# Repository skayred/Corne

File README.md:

# Budget Wireless Corne Keyboard Build

A DIY wireless split keyboard based on the Corne layout, built for approximately $25 USD. This project uses a ProMicro clone with nrf52840 chip, making it a cost-effective alternative to traditional wireless split keyboard builds.

## Features
- Fully wireless using Bluetooth
- Split ergonomic design (Corne layout)
- Low profile design for portability
- Battery-powered with power switch
- ZMK firmware
- Estimated battery life: 1+ month

## Bill of Materials

| Component | Quantity | Cost (USD) | Link |
|-----------|----------|------------|------|
| Controller boards (ProMicro nrf52840) | 2 | 6.82 | [AliExpress](https://a.aliexpress.com/_EIV3vwY) |
| Batteries | 2 | 4.20 | [AliExpress](https://a.aliexpress.com/_Eynt9TK) |
| Mechanical Switches | 50 | 7.47 | [AliExpress](https://a.aliexpress.com/_EGhMxEC) |
| Keycaps | Set | 3.79 | [Option 1](https://a.aliexpress.com/_EzQyNtA) / [Option 2](https://a.aliexpress.com/_EH8mNqs) |
| Diodes (1N4148) | 100 | 0.85 | [AliExpress](https://a.aliexpress.com/_EwZoG2G) |
| Slide Switches | 2 | 0.11 | |
| 3D Printed Parts | Set | 1.80 | Files provided |

**Total Cost**: $25.04 (excluding wires and screws)

## Current Keymap

## Build Instructions

### Prerequisites
- Basic soldering skills
- Access to a 3D printer
- Basic understanding of keyboard firmware

### Case Assembly
1. Print the case files (STL files provided in `3DFiles` directory)
2. Note: You may need to adjust the:
   - Battery compartment size
   - Slide switch holes

### Wiring
1. Wire switches in a matrix configuration
2. Connect diodes:
   - Direction matters (black line indicates cathode)
   - Use diode legs for the rows
   - Use separate wires for columns
3. Keep wiring clear of screw holes
4. Connect the battery:
   - GND to GND pin
   - Positive to one of the side legs on the slide switch
   - Middle pin of the slide switch to the RAW pin

### Pin Connections for Rows and Columns
The matrix configuration uses GPIO pins on the nRF52840 Pro Micro clone. Below are the connections:

#### Rows (Connected to `row-gpios`):
- Row 0: Pin 21
- Row 1: Pin 20
- Row 2: Pin 19
- Row 3: Pin 18

#### Columns (Connected to `col-gpios`):
- Column 0: Pin 2
- Column 1: Pin 7
- Column 2: Pin 6
- Column 3: Pin 5
- Column 4: Pin 4
- Column 5: Pin 3

These pins are defined in the firmware and are configured for GPIO matrix scanning.

### Firmware Setup
This keyboard uses ZMK firmware. The left half acts as the main controller that connects to your device.

To flash the firmware:
1. Double press the reset button
2. Board will appear as mass storage device
3. Flash the appropriate firmware file

If you forgot the keyboard from your device and can't reconnect:
1. Flash the `settings_reset-nice_nano_v2-zmk.uf2` file
2. Reflash the regular firmware
3. Pair

## Repository Structure
```
├── .github/workflows/
│   └── build.yml
├── 3DFiles/
│   ├── Case_Left.stl
│   ├── Case_Right.stl
│   └── PlateCorne.stl
├── config/
│   ├── boards/shields/corne/
│   │   ├── corne_left.conf
│   │   ├── corne_left.overlay
│   │   ├── corne_right.conf
│   │   ├── corne_right.overlay
│   │   ├── corne.conf
│   │   ├── corne.dtsi
│   │   ├── Kconfig.defconfig
│   │   └── Kconfig.shield
│   ├── corne.keymap
│   └── west.yml
├── firmware/
│   ├── corne_left-nice_nano_v2-zmk.uf2
│   ├── corne_right-nice_nano_v2-zmk.uf2
│   └── settings_reset-nice_nano_v2-zmk.uf2
└── zephyr/
    ├── module.yml
    └── build.yaml
```

## Known Issues
- Left side case may have warping issues if battery swells
- Slide switch holes may need adjustment based on your components

## Final result

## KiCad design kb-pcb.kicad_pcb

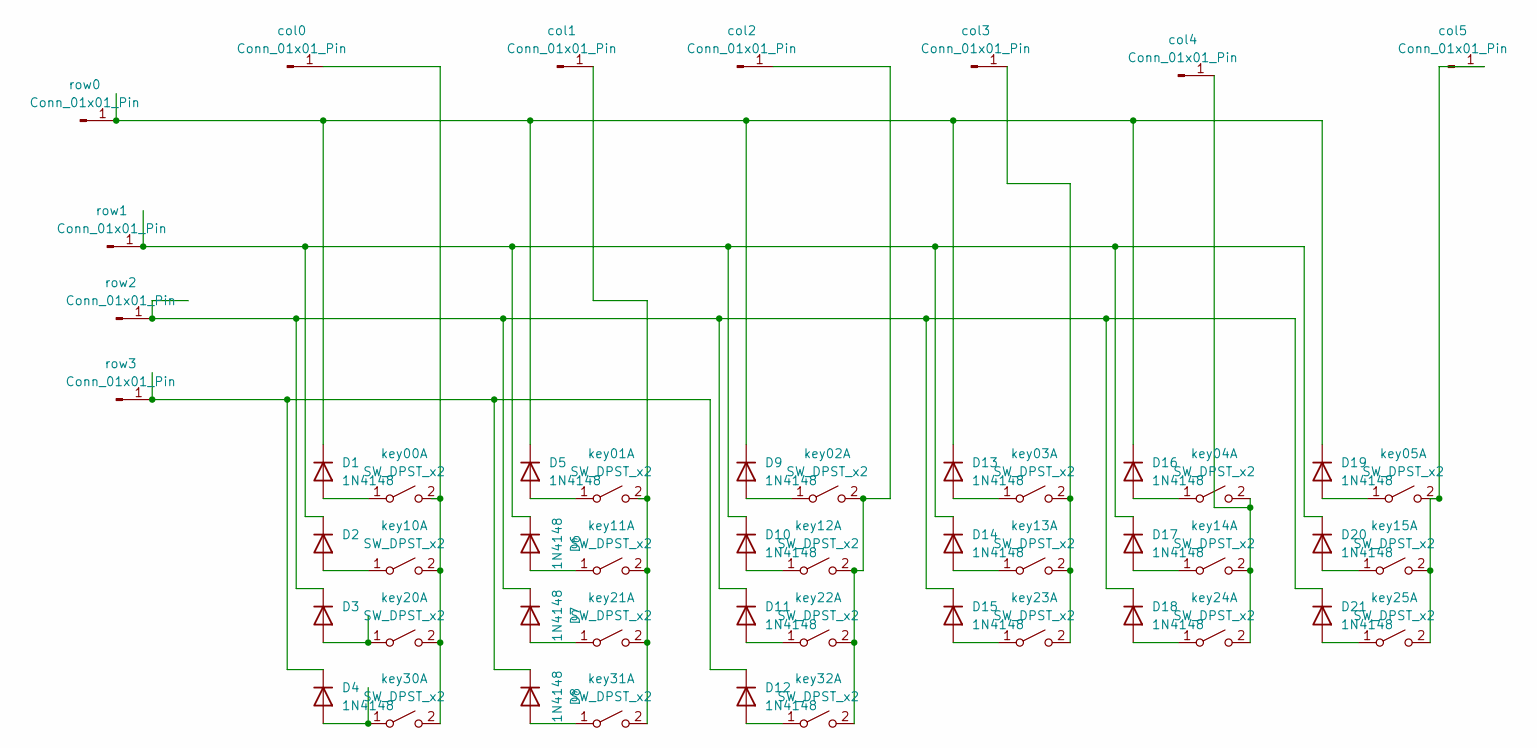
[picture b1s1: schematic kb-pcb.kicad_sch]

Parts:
D1, D2, D3, D4, D5, D6, D7, D8, D9, D10, D11, D12, D13, D14, D15, D16, D17, D18, D19, D20, D21: 1N4148; D_DO-35_SOD27_P7.62mm_Horizontal
col0, col1, col2, col3, col4, col5: Conn_01x01_Pin; PinSocket_1x01_P1.27mm_Vertical
key00, key01, key02, key03, key04, key05, key10, key11, key12, key13, key14, key15, key20, key21, key22, key23, key24, key25, key30, key31, key32: SW_DPST_x2; SW_Redragon_LowProfile_PCB_1.00u
row0, row1, row2, row3: Conn_01x01_Pin; PinSocket_1x01_P1.27mm_Vertical

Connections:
unnamed: D1.2 (A), key00.1 (A)
unnamed: D1.1 (K), D5.1 (K), D9.1 (K), D13.1 (K), D16.1 (K), D19.1 (K), row0.1
unnamed: D2.2 (A), key10.1 (A)
unnamed: D3.2 (A), key20.1 (A)
unnamed: D4.2 (A), key30.1 (A)
unnamed: D5.2 (A), key01.1 (A)
unnamed: D6.2 (A), key11.1 (A)
unnamed: D7.2 (A), key21.1 (A)
unnamed: D8.2 (A), key31.1 (A)
unnamed: D9.2 (A), key02.1 (A)
unnamed: D10.2 (A), key12.1 (A)
unnamed: D2.1 (K), D6.1 (K), D10.1 (K), D14.1 (K), D17.1 (K), D20.1 (K), row1.1
unnamed: D11.2 (A), key22.1 (A)
unnamed: D3.1 (K), D7.1 (K), D11.1 (K), D15.1 (K), D18.1 (K), D21.1 (K), row2.1
unnamed: D12.2 (A), key32.1 (A)
unnamed: D4.1 (K), D8.1 (K), D12.1 (K), row3.1
unnamed: D13.2 (A), key03.1 (A)
unnamed: D14.2 (A), key13.1 (A)
unnamed: D15.2 (A), key23.1 (A)
unnamed: D16.2 (A), key04.1 (A)
unnamed: D17.2 (A), key14.1 (A)
unnamed: D18.2 (A), key24.1 (A)
unnamed: D19.2 (A), key05.1 (A)
unnamed: D20.2 (A), key15.1 (A)
unnamed: D21.2 (A), key25.1 (A)
unnamed: col0.1, key00.2 (B), key10.2 (B), key20.2 (B), key30.2 (B)
unnamed: col1.1, key01.2 (B), key11.2 (B), key21.2 (B), key31.2 (B)
unnamed: col2.1, key02.2 (B), key12.2 (B), key22.2 (B), key32.2 (B)
unnamed: col3.1, key03.2 (B), key13.2 (B), key23.2 (B)
unnamed: col4.1, key04.2 (B), key14.2 (B), key24.2 (B)
unnamed: col5.1, key05.2 (B), key15.2 (B), key25.2 (B)

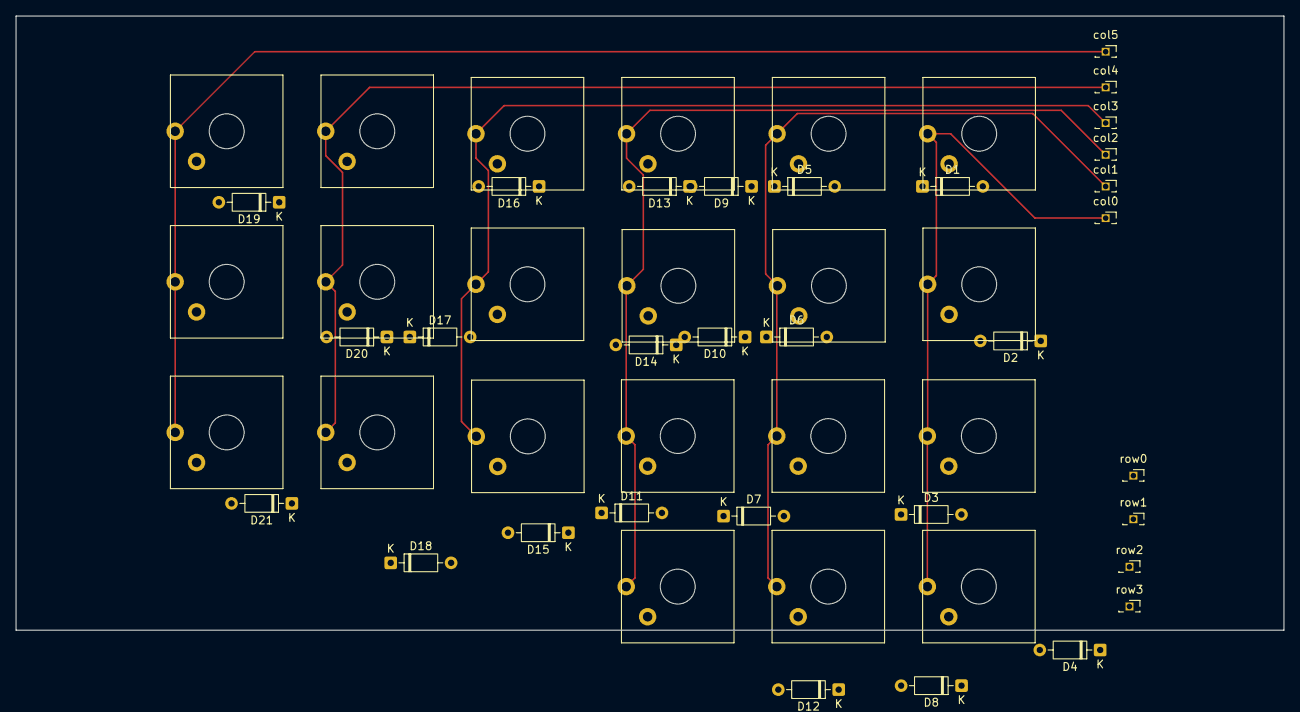
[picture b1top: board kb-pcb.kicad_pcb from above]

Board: 2 copper layers, 160.0 x 77.5 mm, 52 parts (0 on the bottom side), 31 nets.

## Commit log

2025-05-20 Update README.md
    final result added
2025-07-20 Add STEP files for CAD editing (closes #1 )
    Sorry for the delay the STEP files are now included.
2025-08-19 README updated: added instructions for identifying rows and columns ( closes #2 )
2025-08-30 PS/2 added
